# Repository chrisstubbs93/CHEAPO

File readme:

Flight code for $$CHEAPO flight computer

Just a simple uBlox NEO 6 GPS / RFM22B tracker

Should be uploaded to "Arduino Pro or Pro Mini (3.3v, 8MHz) w/ ATmega328"

Main tracker code is CHEAPO.INO in root directory, other code in subfolders should be treated as experimental/untested.

Current hardware CHEAPOv4 http://chris-stubbs.co.uk/wp/?p=352

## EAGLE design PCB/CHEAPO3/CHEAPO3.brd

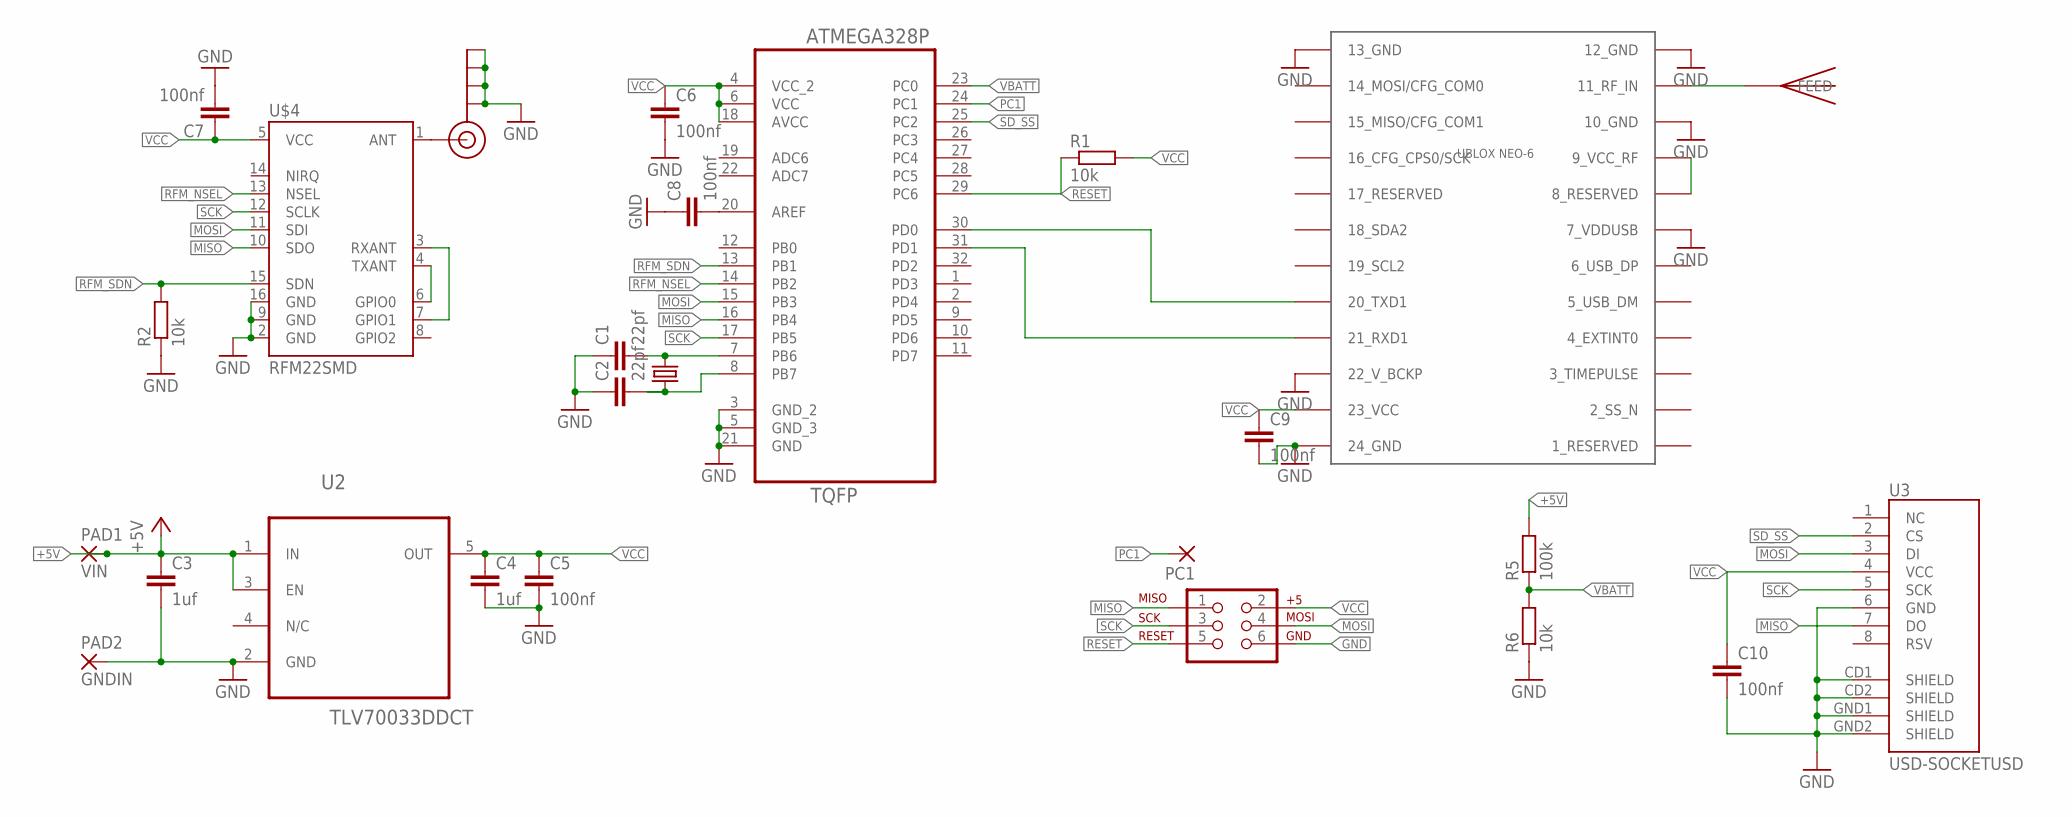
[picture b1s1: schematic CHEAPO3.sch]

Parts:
C1, C2: 22pf; C0603
C3, C4: 1uf; C0603
C5, C6, C7, C8, C9, C10: 100nf; C0603
J1: AVR_SPI_PRG_6PTH; 2X3
J$1: SMA_EDGE; SMA-EDGE
PAD1: VIN; SMD1,27-2,54
PAD2: GNDIN; SMD1,27-2,54
PC1: SMD2; SMD1,27-2,54
R1, R2, R6: 10k; R0603
R5: 100k; R0603
U1: ATMEGA328P-AU; QFP80P900X900X120-32N
U2: TLV70033DDCT; SOT95P280X110-5N
U3: USD-SOCKETUSD; USD-SOCKET-PP
U$1: UBLOX_NEO-6; UBLOX_NEO-6P
U$2: ABRACON_ABM3_CRYSTALABM03_HC49; ABM03_HC49
U$3: JTI_ANTENNA-1575AT43A40
U$4: RFM22SMD; RFM22-XXX-S2

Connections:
+5V: C3.1, PAD1.1, R5.2, U2.1 (IN), U2.3 (EN)
GND: C1.1, C2.1, C3.2, C4.2, C5.2, C6.2, C7.2, C8.1, C9.2, C10.2, J1.6, J$1.GND@0 (GND), J$1.GND@1 (GND), J$1.GND@2 (GND), J$1.GND@3 (GND), PAD2.1, R2.1, R6.1, U1.3 (GND_2), U1.5 (GND_3), U1.21 (GND), U2.2 (GND), U3.6 (GND), U3.CD1 (SHIELD), U3.CD2 (SHIELD), U3.GND1 (SHIELD), U3.GND2 (SHIELD), U$1.7_VDDUSB, U$1.10_GND, U$1.12_GND, U$1.13_GND, U$1.22_V_BCKP, U$1.24_GND, U$4.2 (GND), U$4.9 (GND), U$4.16 (GND)
MISO: J1.1, U1.16 (PB4), U3.7 (DO), U$4.10 (SDO)
MOSI: J1.4, U1.15 (PB3), U3.3 (DI), U$4.11 (SDI)
unnamed: C1.2, U1.7 (PB6), U$2.2
unnamed: C2.2, U1.8 (PB7), U$2.1
unnamed: U$4.4 (TXANT), U$4.6 (GPIO0)
unnamed: U$4.3 (RXANT), U$4.7 (GPIO1)
unnamed: U$1.8_RESERVED, U$1.9_VCC_RF
unnamed: U$1.11_RF_IN, U$3.FEED
unnamed: C8.2, U1.20 (AREF)
unnamed: J$1.SIG (SIGNAL), U$4.1 (ANT)
unnamed: U1.30 (PD0), U$1.20_TXD1
unnamed: U1.31 (PD1), U$1.21_RXD1
PC1: PC1.1, U1.24 (PC1)
RESET: J1.5, R1.1, U1.29 (PC6)
RFM_NSEL: U1.14 (PB2), U$4.13 (NSEL)
RFM_SDN: R2.2, U1.13 (PB1), U$4.15 (SDN)
SCK: J1.3, U1.17 (PB5), U3.5 (SCK), U$4.12 (SCLK)
SD_SS: U1.25 (PC2), U3.2 (CS)
VBATT: R5.1, R6.2, U1.23 (PC0)
VCC: C4.1, C5.1, C6.1, C7.1, C9.1, C10.1, J1.2, R1.2, U1.4 (VCC_2), U1.6 (VCC), U1.18 (AVCC), U2.5 (OUT), U3.4 (VCC), U$1.23_VCC, U$4.5 (VCC)

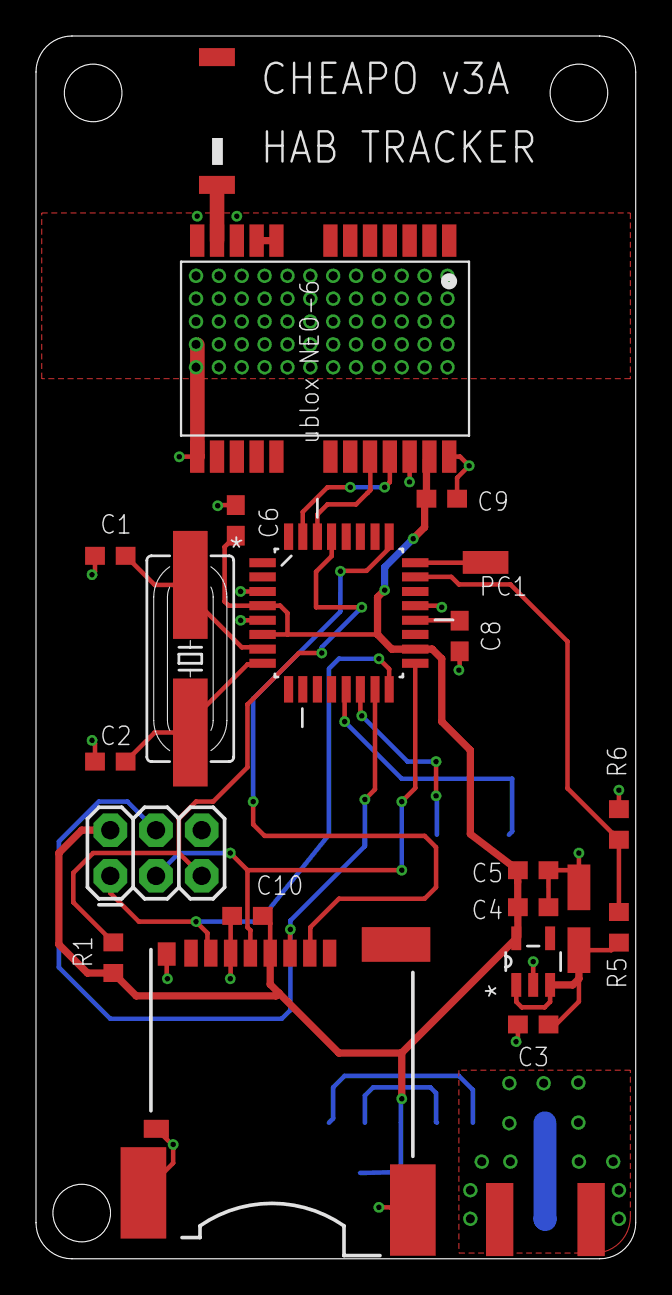
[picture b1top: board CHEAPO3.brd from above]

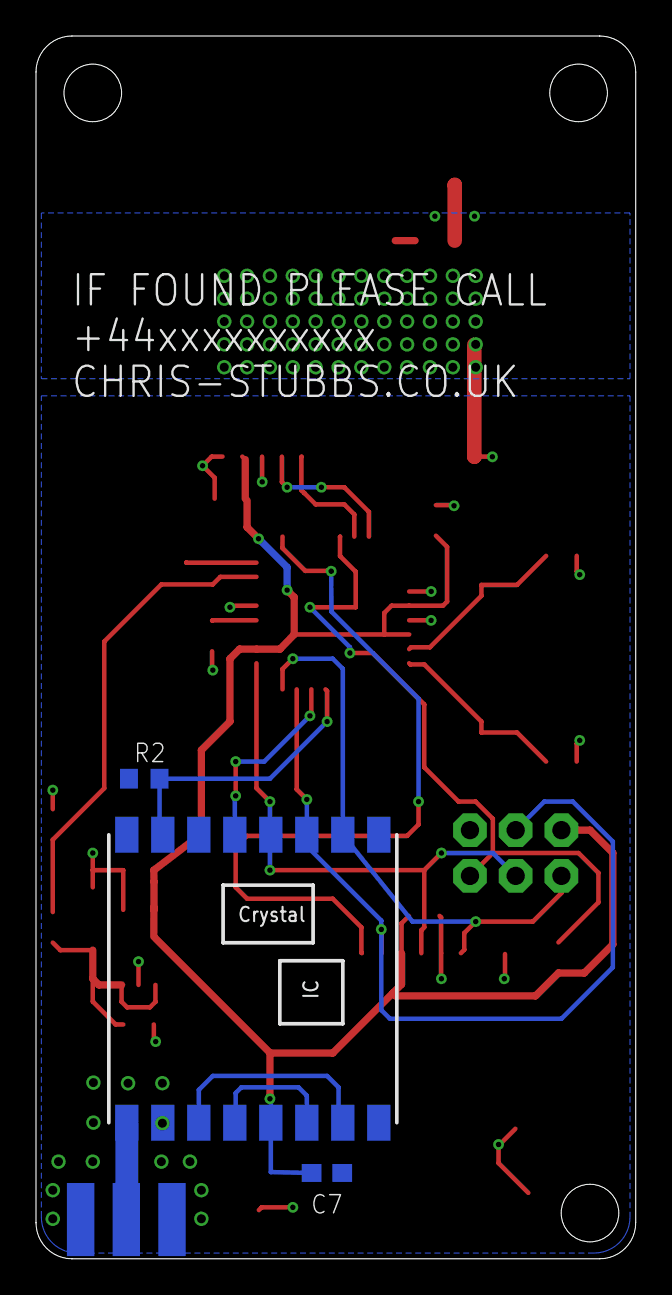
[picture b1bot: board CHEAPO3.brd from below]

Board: 2 copper layers, 33.3 x 67.9 mm, 26 parts (4 on the bottom side), 22 nets.

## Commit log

2013-03-24 CHEAPO code added, NOT FLIGHT READY
    All working. probably could fly. need to add RFM22B power cycling.
2013-03-24 Added power cycling code & optimised. needs testing
2013-03-27 Sats = 0 with no fix & comments
    Sats now = 0 when there is no new GPS data. Added a few comments.
    restart interval and radio power are now defined at the top. Power
    cycling is tested and seems to work, but code is pretty bad.
2013-04-21 Fixed padding on time & unsigned int altitude
    The code worked fine in flight apart from dropping the first 0 in times
    before 10AM eg 064500 was printed as 64500. That should now be fixed.
    Altitude has also been changed to an unsigned int to allow altitudes of
    up to 65535m
2013-05-26 AFC code added to another folder
    AFC works but is too jumpy for use
2013-06-01 Added vbatt reading
2013-06-01 Tidied and commented
2013-06-04 Added temp sensing
    Temp sensing calibrated for CHEAPO v3A1
2013-06-24 Added SD only code
2013-07-23 808 code added DO NOT FLY
2013-07-24 nav mode settings changed
2013-08-23 Navmode settings changed
    Navmode is set every second in case of reset >12k
2013-09-11 Tidied comments and changed sats
    should send stats whilst acquiring
2013-11-11 GPS Sats only set after lock
    Code tidied
    Sats is only set after lock now as tinygps will only report back sats if
    it has a 2d/3d fix anyway and we were getting crazy values.
2013-11-17 >= 5 sats for PSM
2013-11-17 Readme updated (successfully flight tested)
    Flight tested to 24km
2013-12-28 Added PCB eagle files
2013-12-28 Added eagle PCB files

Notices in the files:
parts and their libraries:
SparkFun-RF: Licensing: CC v3.0 Share-Alike You are welcome to use this library for commercial purposes.
